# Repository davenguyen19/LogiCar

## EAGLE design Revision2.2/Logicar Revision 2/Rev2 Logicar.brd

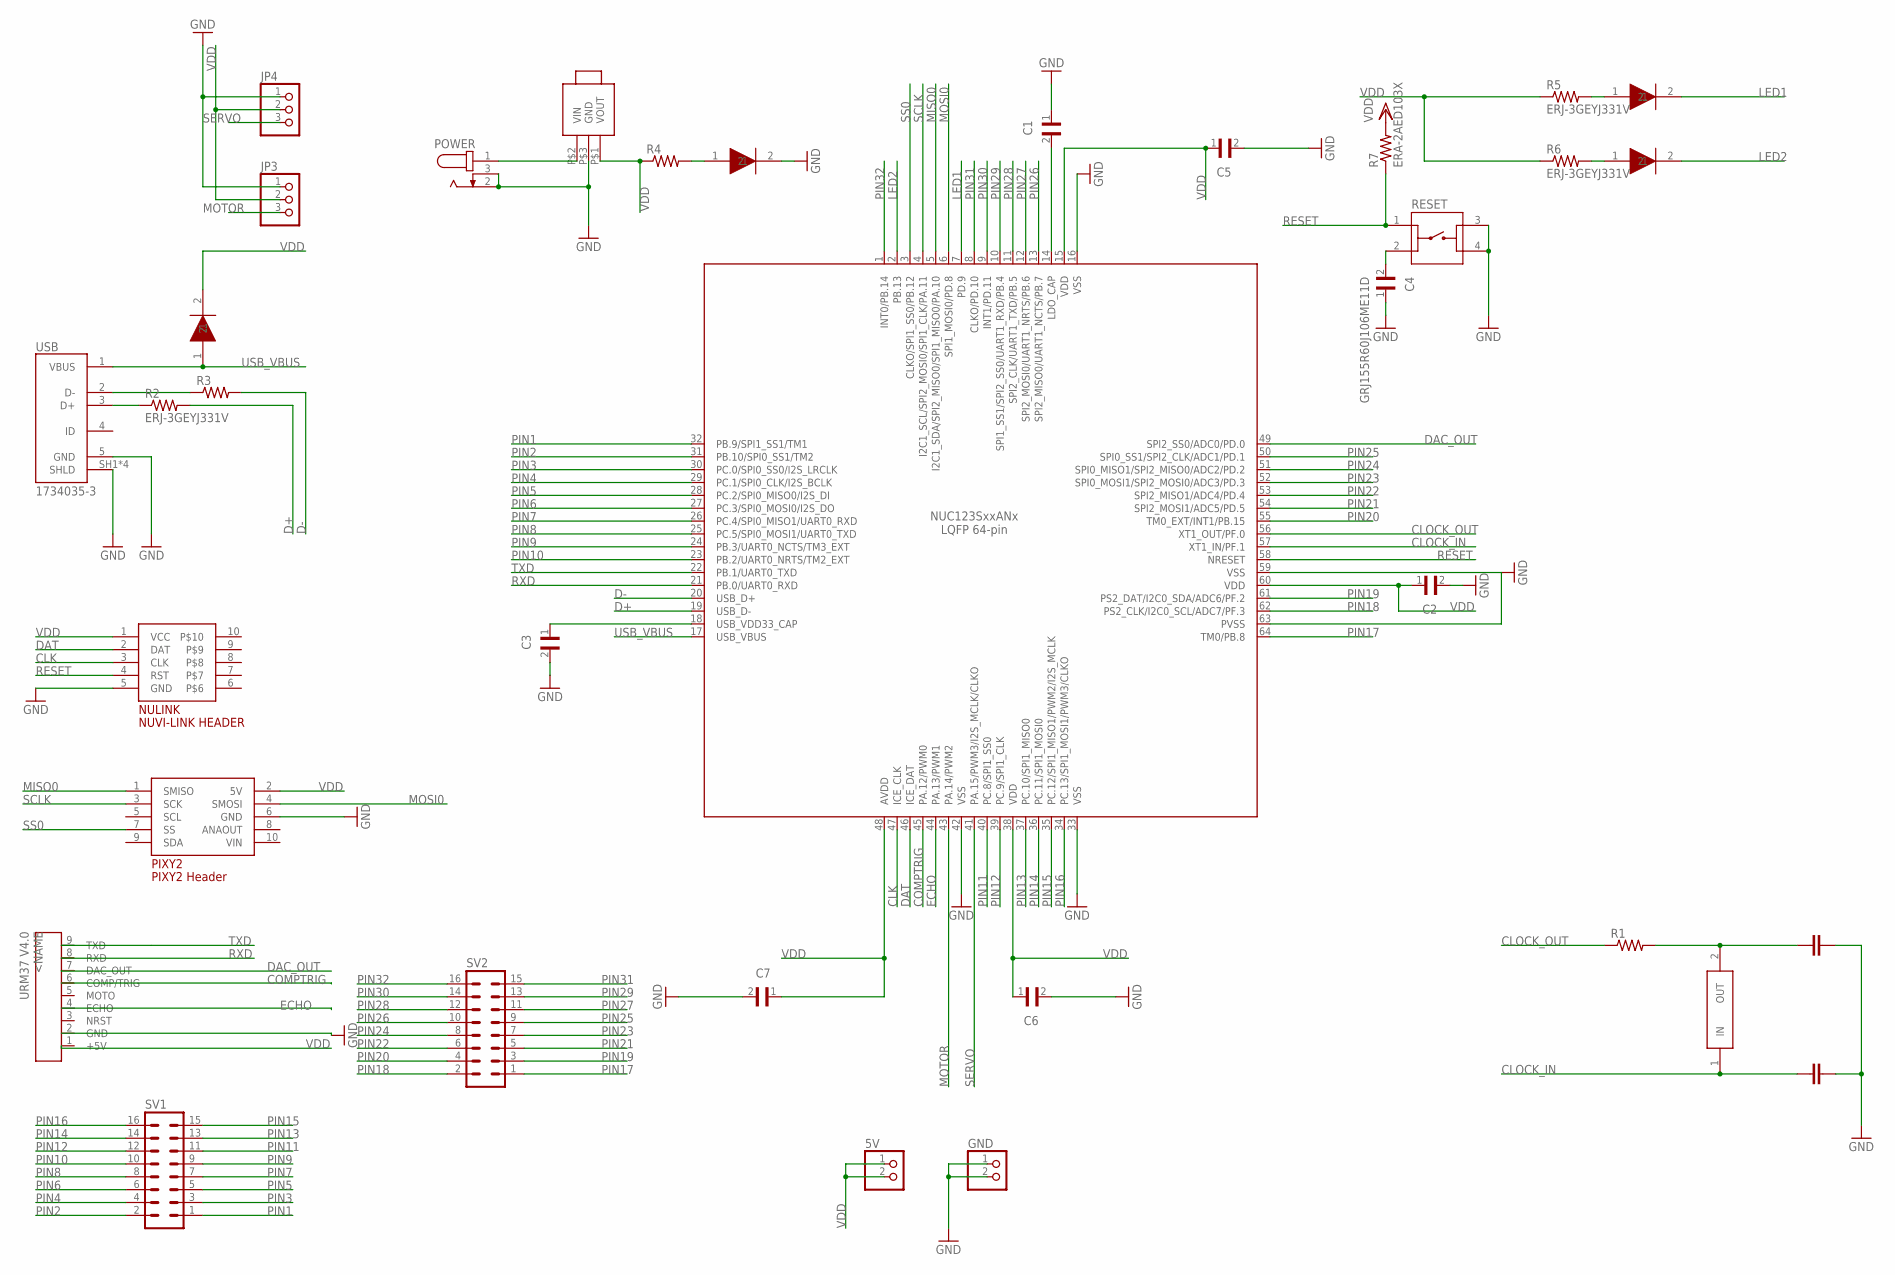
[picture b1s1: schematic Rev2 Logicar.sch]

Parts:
5V: PINHD-1X2; 1X02
18UF, 18UF1: 18UF_CAPACITOR; CAPC1608X70
C1: F380J476MMAAXEH3; CAPC1608X90
C2, C3, C5, C6, C7: CL21F104ZBCNNNC; CAPC2012X140N
C4: GRJ155R60J106ME11D; CAPC1005X55N
GND: PINHD-1X2; 1X02
JP3, JP4: PINHD-1X3; 1X03
LED1, LED2: LED; LEDC2408X70
NUC123: NUC123SD4AN0-ND; QFP40P900X900X160-64
NULINK: NUVI-LINK
PIXY2: PIXY2HEADER; PIXY2PIN
POWER: PJ-202A; CUI_PJ-202A
PWR_LED: LED; LEDC2408X70
R1, R2, R3, R4, R5, R6: ERJ-3GEYJ331V; RESC1608X55
R7: ERA-2AED103X; RESC1005X40
RESET: 1825910-6; SW_1825910-6-4
SV1, SV2: MA08-2
U$2: CRYSTAL_OSS; XTAL1145X470X420
U$8: NCP5501; DPAK3
ULTRASONIC: 1X9PINROW_MALE; HDRV9W64P254_1X9_1016X508X838B
USB: 1734035-3; TE_1734035-3
USB_LED: LED; LEDC2408X70

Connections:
CLK: NUC123.47 (ICE_CLK), NULINK.3 (CLK)
CLOCK_IN: 18UF.1, NUC123.57 (XT1_IN/PF.1), U$2.1 (IN)
CLOCK_OUT: NUC123.56 (XT1_OUT/PF.0), R1.1
COMPTRIG: NUC123.45 (PA.12/PWM0), ULTRASONIC.6 (COMP/TRIG)
D+: NUC123.19 (USB_D-), R2.2
D-: NUC123.20 (USB_D+), R3.2
DAC_OUT: NUC123.49 (SPI2_SS0/ADC0/PD.0), ULTRASONIC.7 (DAC_OUT)
DAT: NUC123.46 (ICE_DAT), NULINK.2 (DAT)
ECHO: NUC123.44 (PA.13/PWM1), ULTRASONIC.4 (ECHO)
GND: 18UF.2, 18UF1.2, C1.1, C2.2, C3.2, C4.1, C5.2, C6.2, C7.2, GND.1, GND.2, JP3.1, JP4.1, NUC123.16 (VSS), NUC123.33 (VSS), NUC123.42 (VSS), NUC123.59 (VSS), NUC123.63 (PVSS), NULINK.5 (GND), PIXY2.6 (GND), POWER.2, POWER.3, PWR_LED.2, RESET.3, RESET.4, U$8.P$3 (GND), ULTRASONIC.2 (GND), USB.5 (GND), USB.SH1 (SHLD), USB.SH2 (SHLD), USB.SH3 (SHLD), USB.SH4 (SHLD)
LED1: LED1.2, NUC123.7 (PD.9)
LED2: LED2.2, NUC123.2 (PB.13)
MISO0: NUC123.5 (I2C1_SDA/SPI2_MISO0/SPI1_MISO0/PA.10), PIXY2.1 (SMISO)
MOSI0: NUC123.6 (SPI1_MOSI0/PD.8), PIXY2.4 (SMOSI)
MOTOR: JP3.3, NUC123.43 (PA.14/PWM2)
unnamed: C3.1, NUC123.18 (USB_VDD33_CAP)
unnamed: C1.2, NUC123.14 (LDO_CAP)
unnamed: 18UF1.1, R1.2, U$2.2 (OUT)
unnamed: C4.2, RESET.2
unnamed: R2.1, USB.3 (D+)
unnamed: R3.1, USB.2 (D-)
unnamed: PWR_LED.1, R4.2
unnamed: POWER.1, U$8.P$2 (VIN)
unnamed: LED1.1, R5.2
unnamed: LED2.1, R6.2
PIN1: NUC123.32 (PB.9/SPI1_SS1/TM1), SV1.1
PIN2: NUC123.31 (PB.10/SPI0_SS1/TM2), SV1.2
PIN3: NUC123.30 (PC.0/SPI0_SS0/I2S_LRCLK), SV1.3
PIN4: NUC123.29 (PC.1/SPI0_CLK/I2S_BCLK), SV1.4
PIN5: NUC123.28 (PC.2/SPI0_MISO0/I2S_DI), SV1.5
PIN6: NUC123.27 (PC.3/SPI0_MOSI0/I2S_DO), SV1.6
PIN7: NUC123.26 (PC.4/SPI0_MISO1/UART0_RXD), SV1.7
PIN8: NUC123.25 (PC.5/SPI0_MOSI1/UART0_TXD), SV1.8
PIN9: NUC123.24 (PB.3/UART0_NCTS/TM3_EXT), SV1.9
PIN10: NUC123.23 (PB.2/UART0_NRTS/TM2_EXT), SV1.10
PIN11: NUC123.40 (PC.8/SPI1_SS0), SV1.11
PIN12: NUC123.39 (PC.9/SPI1_CLK), SV1.12
PIN13: NUC123.37 (PC.10/SPI1_MISO0), SV1.13
PIN14: NUC123.36 (PC.11/SPI1_MOSI0), SV1.14
PIN15: NUC123.35 (PC.12/SPI1_MISO1/PWM2/I2S_MCLK), SV1.15
PIN16: NUC123.34 (PC.13/SPI1_MOSI1/PWM3/CLKO), SV1.16
PIN17: NUC123.64 (TM0/PB.8), SV2.1
PIN18: NUC123.62 (PS2_CLK/I2C0_SCL/ADC7/PF.3), SV2.2
PIN19: NUC123.61 (PS2_DAT/I2C0_SDA/ADC6/PF.2), SV2.3
PIN20: NUC123.55 (TM0_EXT/INT1/PB.15), SV2.4
PIN21: NUC123.54 (SPI2_MOSI1/ADC5/PD.5), SV2.5
PIN22: NUC123.53 (SPI2_MISO1/ADC4/PD.4), SV2.6
PIN23: NUC123.52 (SPI0_MOSI1/SPI2_MOSI0/ADC3/PD.3), SV2.7
PIN24: NUC123.51 (SPI0_MISO1/SPI2_MISO0/ADC2/PD.2), SV2.8
PIN25: NUC123.50 (SPI0_SS1/SPI2_CLK/ADC1/PD.1), SV2.9
PIN26: NUC123.13 (SPI2_MISO0/UART1_NCTS/PB.7), SV2.10
PIN27: NUC123.12 (SPI2_MOSI0/UART1_NRTS/PB.6), SV2.11
PIN28: NUC123.11 (SPI2_CLK/UART1_TXD/PB.5), SV2.12
PIN29: NUC123.10 (SPI1_SS1/SPI2_SS0/UART1_RXD/PB.4), SV2.13
PIN30: NUC123.9 (INT1/PD.11), SV2.14
PIN31: NUC123.8 (CLKO/PD.10), SV2.15
PIN32: NUC123.1 (INT0/PB.14), SV2.16
RESET: NUC123.58 (NRESET), NULINK.4 (RST), R7.1, RESET.1
RXD: NUC123.21 (PB.0/UART0_RXD), ULTRASONIC.8 (RXD)
SCLK: NUC123.4 (I2C1_SCL/SPI2_MOSI0/SPI1_CLK/PA.11), PIXY2.3 (SCK)
SERVO: JP4.3, NUC123.41 (PA.15/PWM3/I2S_MCLK/CLKO)
SS0: NUC123.3 (CLKO/SPI1_SS0/PB.12), PIXY2.7 (SS)
TXD: NUC123.22 (PB.1/UART0_TXD), ULTRASONIC.9 (TXD)
USB_VBUS: NUC123.17 (USB_VBUS), USB.1 (VBUS), USB_LED.1
VDD: 5V.1, 5V.2, C2.1, C5.1, C6.1, C7.1, JP3.2, JP4.2, NUC123.15 (VDD), NUC123.38 (VDD), NUC123.48 (AVDD), NUC123.60 (VDD), NULINK.1 (VCC), PIXY2.2 (5V), R4.1, R5.1, R6.1, R7.2, U$8.P$1 (VOUT), ULTRASONIC.1 (+5V), USB_LED.2

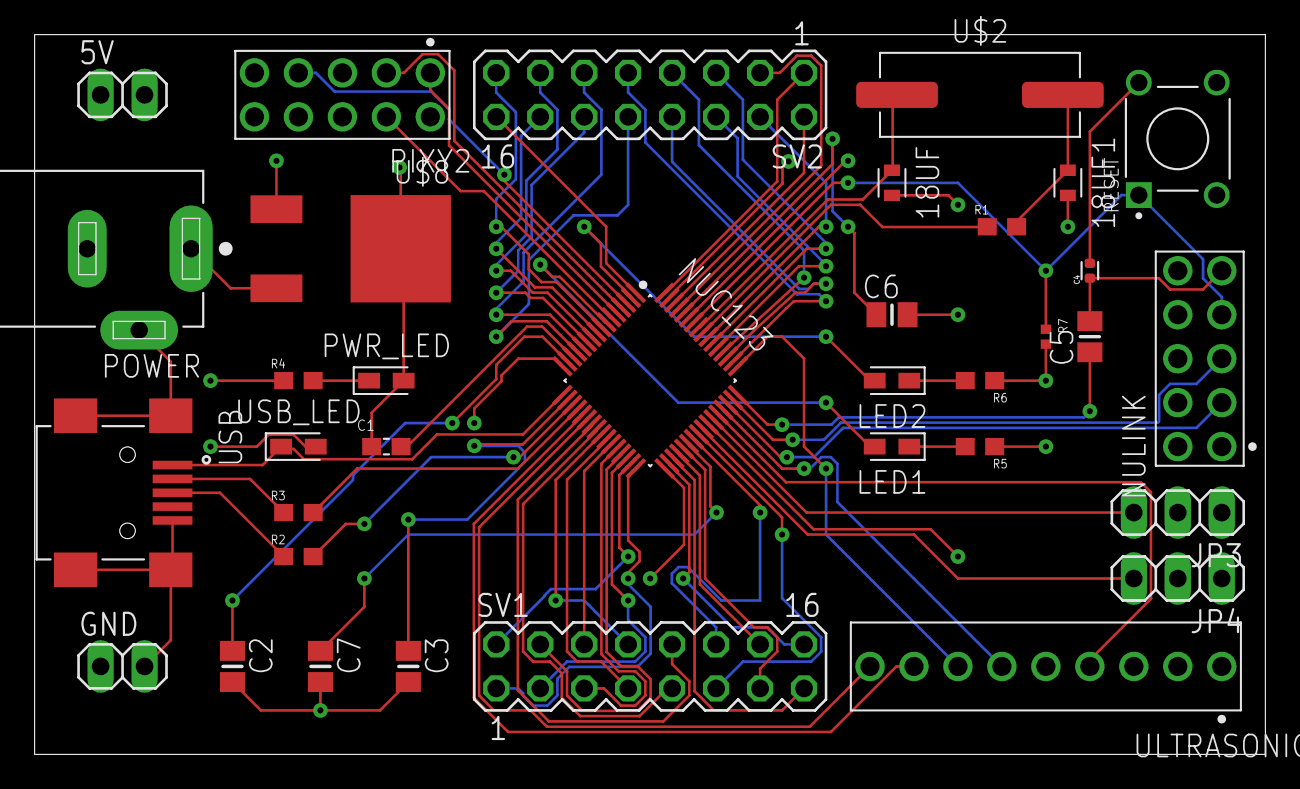
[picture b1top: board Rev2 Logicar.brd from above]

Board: 4 copper layers, 71.1 x 41.6 mm, 35 parts (0 on the bottom side), 65 nets.

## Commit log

2019-05-03 files added
2019-05-03 UltraSonic CapCode
2019-05-03 Cleaning stuff
2019-05-03 File names
2019-05-03 More Cleanup
